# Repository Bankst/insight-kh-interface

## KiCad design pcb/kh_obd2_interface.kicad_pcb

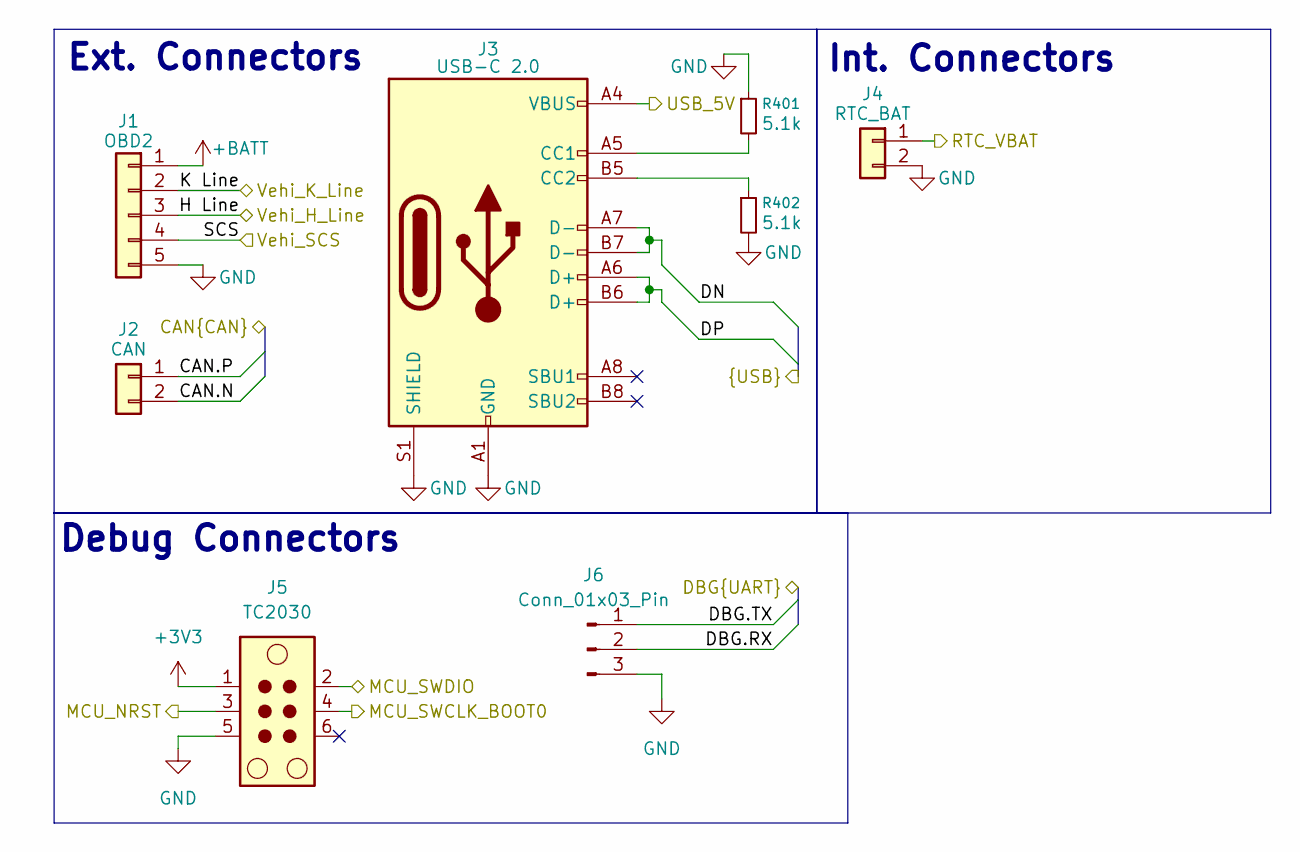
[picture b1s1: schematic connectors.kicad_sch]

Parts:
J1: OBD2; Molex_SL_171971-0005_1x05_P2.54mm_Vertical
J2: CAN; Molex_SL_171971-0002_1x02_P2.54mm_Vertical
J3: USB-C 2.0; USB_C_Receptacle_GCT_USB4105-xx-A_16P_TopMnt_Horizontal
J4: RTC_BAT; Molex_PicoBlade_53047-0210_1x02_P1.25mm_Vertical
J5: TC2030; Tag-Connect_TC2030-IDC-NL_2x03_P1.27mm_Vertical
J6: Conn_01x03_Pin; PinHeader_1x03_P2.54mm_Vertical_SMD_Pin1Left
R401, R402: 5.1k; R_0402_1005Metric

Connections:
+3V3: J5.1; also elsewhere on the board
+BATT: J1.1; also elsewhere on the board
/Communications/CAN.N: J2.2; also elsewhere on the board
/Communications/CAN.P: J2.1; also elsewhere on the board
/Connectors/DBG.RX: J6.2; also elsewhere on the board
/Connectors/DBG.TX: J6.1; also elsewhere on the board
/Connectors/DN: J3.A7 (D-), J3.B7 (D-); also elsewhere on the board
/Connectors/DP: J3.A6 (D+), J3.B6 (D+); also elsewhere on the board
/Connectors/H Line: J1.3; also elsewhere on the board
/Connectors/K Line: J1.2; also elsewhere on the board
/Connectors/MCU_NRST: J5.3; also elsewhere on the board
/Connectors/MCU_SWCLK_BOOT0: J5.4; also elsewhere on the board
/Connectors/MCU_SWDIO: J5.2; also elsewhere on the board
/Connectors/RTC_VBAT: J4.1; also elsewhere on the board
/Connectors/SCS: J1.4; also elsewhere on the board
/Connectors/USB_5V: J3.A4 (VBUS), J3.A9 (VBUS), J3.B4 (VBUS), J3.B9 (VBUS); also elsewhere on the board
GND: J1.5, J3.A1 (GND), J3.A12 (GND), J3.B1 (GND), J3.B12 (GND), J3.S1 (SHIELD), J4.2, J5.5, J6.3, R401.1, R402.2; also elsewhere on the board
unnamed: J3.A5 (CC1), R401.2
unnamed: J3.B5 (CC2), R402.1

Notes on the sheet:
Int. Connectors
Debug Connectors
Ext. Connectors

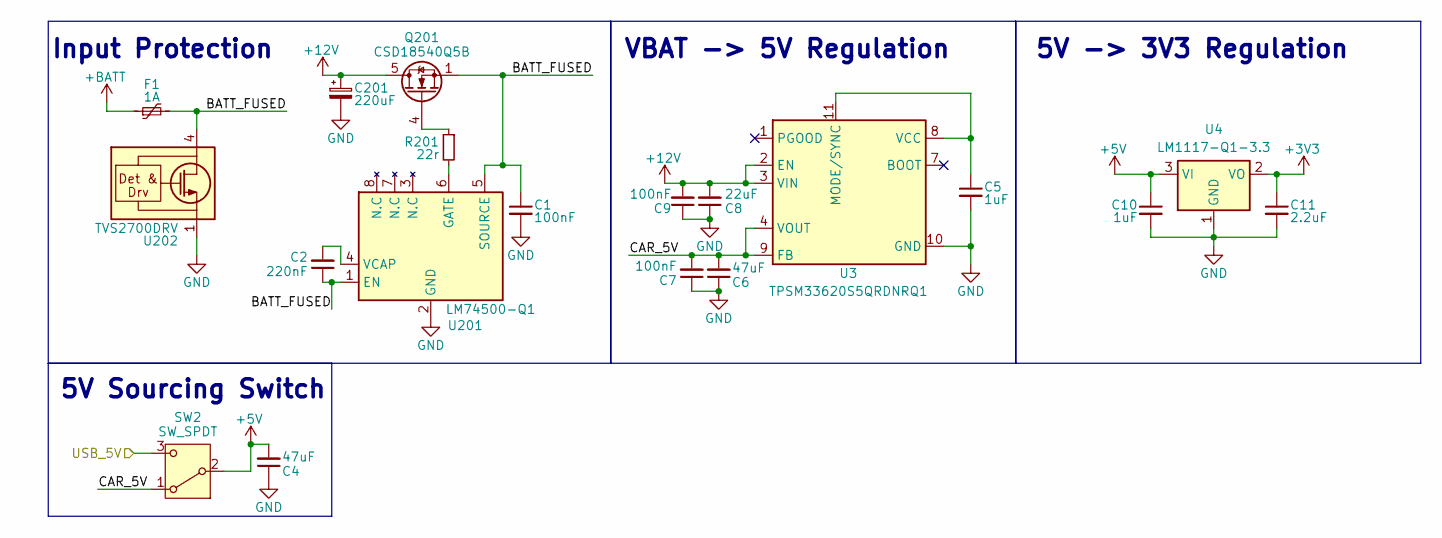
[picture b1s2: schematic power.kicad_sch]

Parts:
C1, C7, C9: 100nF; C_0402_1005Metric; Part C1005X5R1H104K050BB
C2: 220nF; C_0402_1005Metric
C4, C6: 47uF; C_1206_3216Metric; Part GRM31CR61A476KE15L
C5, C10: 1uF; C_0402_1005Metric; Part GRM155R71C104KA88D
C8: 22uF; C_1210_3225Metric; Part GRM32ER61E226KE15L
C11: 2.2uF; C_0402_1005Metric; Part GRM155R71C104KA88D
C201: 220uF; C_Elec_6.3x5.8; Part UWT1H221MNL1GS
F1: 1A; Fuse_1812_4532Metric; Part 1812L110/33MR
Q201: CSD18540Q5B; TDSON-8-1
R201: 22r; R_0402_1005Metric
SW2: SW_SPDT; PinHeader_1x03_P2.54mm_Vertical_SMD_Pin1Left
U3: TPSM33620S5QRDNRQ1; Texas_B3QFN-14-1EP_5x5.5mm_P0.65mm_ThermalVia
U4: LM1117-Q1-3.3; SOT-223-3_TabPin2; Part PLM111733QDCYRQ1
U201: LM74500-Q1; SOT-23-8
U202: TVS2700DRV; WSON-6-1EP_2x2mm_P0.65mm_EP1x1.6mm

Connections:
+3V3: C11.1, U4.2 (VO); also elsewhere on the board
+5V: C4.2, C10.1, SW2.2 (B), U4.3 (VI); also elsewhere on the board
+12V: C8.2, C9.2, C201.1, Q201.5 (D), U3.2 (EN), U3.3 (VIN); also elsewhere on the board
+BATT: F1.1; also elsewhere on the board
/Connectors/USB_5V: SW2.3 (C); also elsewhere on the board
/Power/BATT_FUSED: C1.1, C2.1, F1.2, Q201.1 (S), Q201.2 (S), Q201.3 (S), U201.1 (EN), U201.5 (SOURCE), U202.4 (IN), U202.5 (IN), U202.6 (IN)
/Power/CAR_5V: C6.2, C7.2, SW2.1 (A), U3.4 (VOUT), U3.9 (FB)
GND: C1.2, C4.1, C5.2, C6.1, C7.1, C8.1, C9.1, C10.2, C11.2, C201.2, U3.10 (GND), U4.1 (GND), U201.2 (GND), U202.1 (GND), U202.2 (GND), U202.3 (GND), U202.7 (GND); also elsewhere on the board
unnamed: Q201.4 (G), R201.1
unnamed: C5.1, U3.8 (VCC), U3.11 (MODE/SYNC)
unnamed: R201.2, U201.6 (GATE)
unnamed: C2.2, U201.4 (VCAP)

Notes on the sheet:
VBAT -> 5V Regulation
5V -> 3V3 Regulation
5V Sourcing Switch
Input Protection

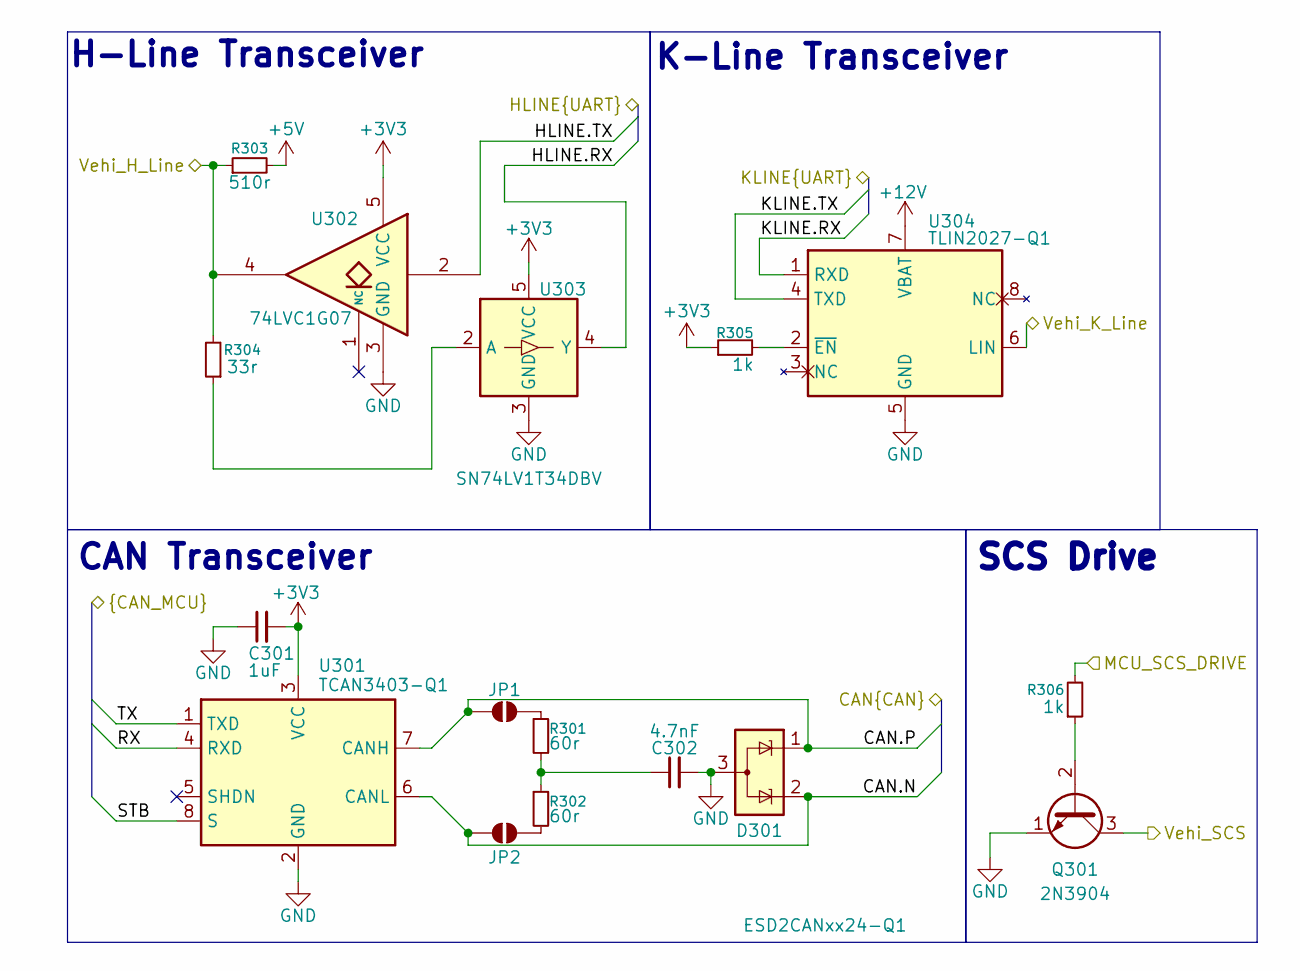
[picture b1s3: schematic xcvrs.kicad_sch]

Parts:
C301: 1uF; C_0402_1005Metric
C302: 4.7nF; C_0402_1005Metric
D301: ESD2CANxx24-Q1; SOT-23-3; Part ESD2CANFD24-Q1
JP1, JP2: SolderJumper_2_Open; SolderJumper-2_P1.3mm_Open_RoundedPad1.0x1.5mm
Q301: 2N3904; SOT-23
R301, R302: 60r; R_0402_1005Metric
R303: 510r; R_0402_1005Metric
R304: 33r; R_0402_1005Metric
R305, R306: 1k; R_0402_1005Metric
U301: TCAN3403-Q1; TSOT-23-8; Part TCAN3403DRQ1
U302: 74LVC1G07; Texas_R-PDSO-G5_DCK-5
U303: SN74LV1T34DBV; SOT-23-5
U304: TLIN2027-Q1; SOIC-8_3.9x4.9mm_P1.27mm

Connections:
+3V3: C301.2, R305.1, U301.3 (VCC), U302.5 (VCC), U303.5 (VCC); also elsewhere on the board
+5V: R303.2; also elsewhere on the board
+12V: U304.7 (VBAT); also elsewhere on the board
/Communications/CAN.N: D301.2 (K), JP2.2 (B), U301.6 (CANL); also elsewhere on the board
/Communications/CAN.P: D301.1 (K), JP1.1 (A), U301.7 (CANH); also elsewhere on the board
/Communications/HLINE.RX: U303.4 (Y); also elsewhere on the board
/Communications/HLINE.TX: U302.2; also elsewhere on the board
/Communications/KLINE.RX: U304.1 (RXD); also elsewhere on the board
/Communications/KLINE.TX: U304.4 (TXD); also elsewhere on the board
/Communications/MCU_SCS_DRIVE: R306.2; also elsewhere on the board
/Communications/RX: U301.4 (RXD); also elsewhere on the board
/Communications/STB: U301.8 (S); also elsewhere on the board
/Communications/TX: U301.1 (TXD); also elsewhere on the board
/Connectors/H Line: R303.1, R304.2, U302.4; also elsewhere on the board
/Connectors/K Line: U304.6 (LIN); also elsewhere on the board
/Connectors/SCS: Q301.3 (C); also elsewhere on the board
GND: C301.1, C302.2, D301.3 (A), Q301.1 (E), U301.2 (GND), U302.3 (GND), U303.3 (GND), U304.5 (GND); also elsewhere on the board
unnamed: C302.1, R301.2, R302.1
unnamed: JP1.2 (B), R301.1
unnamed: JP2.1 (A), R302.2
unnamed: Q301.2 (B), R306.1
unnamed: R304.1, U303.2 (A)
unnamed: R305.2, U304.2 (~EN)

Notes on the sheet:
CAN Transceiver
SCS Drive
K-Line Transceiver
H-Line Transceiver

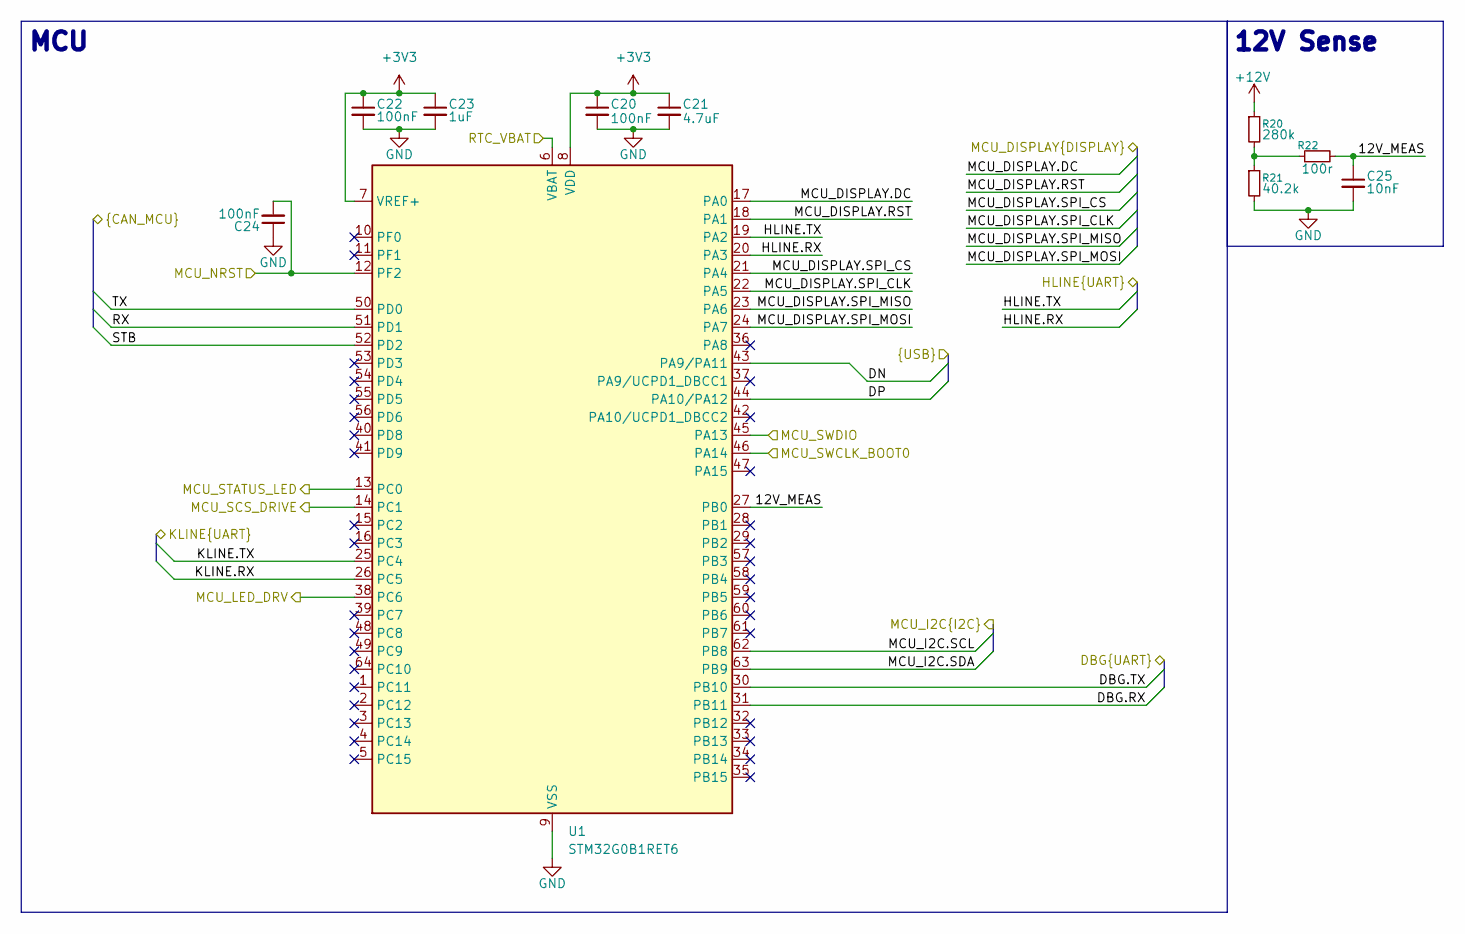
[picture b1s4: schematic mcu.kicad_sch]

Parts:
C20, C22, C24: 100nF; C_0402_1005Metric
C21: 4.7uF; C_0402_1005Metric
C23: 1uF; C_0402_1005Metric
C25: 10nF; C_0402_1005Metric
R20: 280k; R_0402_1005Metric
R21: 40.2k; R_0402_1005Metric
R22: 100r; R_0402_1005Metric
U1: STM32G0B1RET6; LQFP-64_10x10mm_P0.5mm

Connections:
+3V3: C20.1, C21.1, C22.1, C23.1, U1.7 (VREF+), U1.8 (VDD); also elsewhere on the board
+12V: R20.1; also elsewhere on the board
/Communications/HLINE.RX: U1.20 (PA3); also elsewhere on the board
/Communications/HLINE.TX: U1.19 (PA2); also elsewhere on the board
/Communications/KLINE.RX: U1.26 (PC5); also elsewhere on the board
/Communications/KLINE.TX: U1.25 (PC4); also elsewhere on the board
/Communications/MCU_SCS_DRIVE: U1.14 (PC1); also elsewhere on the board
/Communications/RX: U1.51 (PD1); also elsewhere on the board
/Communications/STB: U1.52 (PD2); also elsewhere on the board
/Communications/TX: U1.50 (PD0); also elsewhere on the board
/Connectors/DBG.RX: U1.31 (PB11); also elsewhere on the board
/Connectors/DBG.TX: U1.30 (PB10); also elsewhere on the board
/Connectors/DN: U1.43 (PA9/PA11); also elsewhere on the board
/Connectors/DP: U1.44 (PA10/PA12); also elsewhere on the board
/Connectors/MCU_NRST: C24.2, U1.12 (PF2); also elsewhere on the board
/Connectors/MCU_SWCLK_BOOT0: U1.46 (PA14); also elsewhere on the board
/Connectors/MCU_SWDIO: U1.45 (PA13); also elsewhere on the board
/Connectors/RTC_VBAT: U1.6 (VBAT); also elsewhere on the board
/HMI/MCU_LED_DRV: U1.38 (PC6); also elsewhere on the board
/HMI/MCU_STATUS_LED: U1.13 (PC0); also elsewhere on the board
/MCU/12V_MEAS: C25.1, R22.2, U1.27 (PB0)
/MCU/MCU_DISPLAY.DC: U1.17 (PA0)
/MCU/MCU_DISPLAY.RST: U1.18 (PA1)
/MCU/MCU_DISPLAY.SPI_CLK: U1.22 (PA5)
/MCU/MCU_DISPLAY.SPI_CS: U1.21 (PA4)
/MCU/MCU_DISPLAY.SPI_MISO: U1.23 (PA6)
/MCU/MCU_DISPLAY.SPI_MOSI: U1.24 (PA7)
/MCU/MCU_I2C.SCL: U1.62 (PB8)
/MCU/MCU_I2C.SDA: U1.63 (PB9)
GND: C20.2, C21.2, C22.2, C23.2, C24.1, C25.2, R21.2, U1.9 (VSS); also elsewhere on the board
unnamed: R20.2, R21.1, R22.1

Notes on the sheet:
12V Sense
MCU

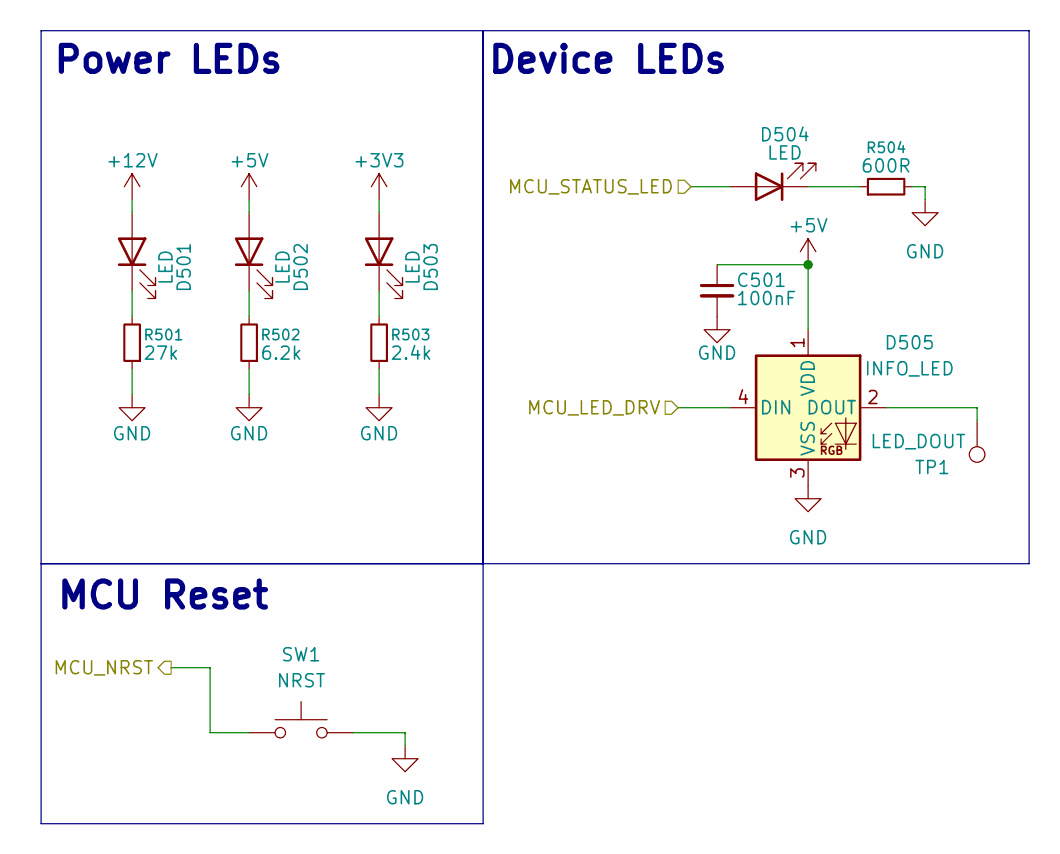
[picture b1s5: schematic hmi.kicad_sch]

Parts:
C501: 100nF; C_0402_1005Metric
D501, D502, D503, D504: LED; LED_0603_1608Metric
D505: INFO_LED; LED_WS2812B_PLCC4_5.0x5.0mm_P3.2mm
R501: 27k; R_0402_1005Metric
R502: 6.2k; R_0402_1005Metric
R503: 2.4k; R_0402_1005Metric
R504: 600R; R_0402_1005Metric
SW1: NRST; SW_Push_SPST_NO_Alps_SKRK
TP1: LED_DOUT; TestPoint_Pad_1.0x1.0mm

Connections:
+3V3: D503.2 (A); also elsewhere on the board
+5V: C501.1, D502.2 (A), D505.1 (VDD); also elsewhere on the board
+12V: D501.2 (A); also elsewhere on the board
/Connectors/MCU_NRST: SW1.1; also elsewhere on the board
/HMI/MCU_LED_DRV: D505.4 (DIN); also elsewhere on the board
/HMI/MCU_STATUS_LED: D504.2 (A); also elsewhere on the board
GND: C501.2, D505.3 (VSS), R501.1, R502.1, R503.1, R504.2, SW1.2; also elsewhere on the board
unnamed: D501.1 (K), R501.2
unnamed: D502.1 (K), R502.2
unnamed: D503.1 (K), R503.2
unnamed: D504.1 (K), R504.1
unnamed: D505.2 (DOUT), TP1.1

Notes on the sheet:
Power LEDs
Device LEDs
MCU Reset

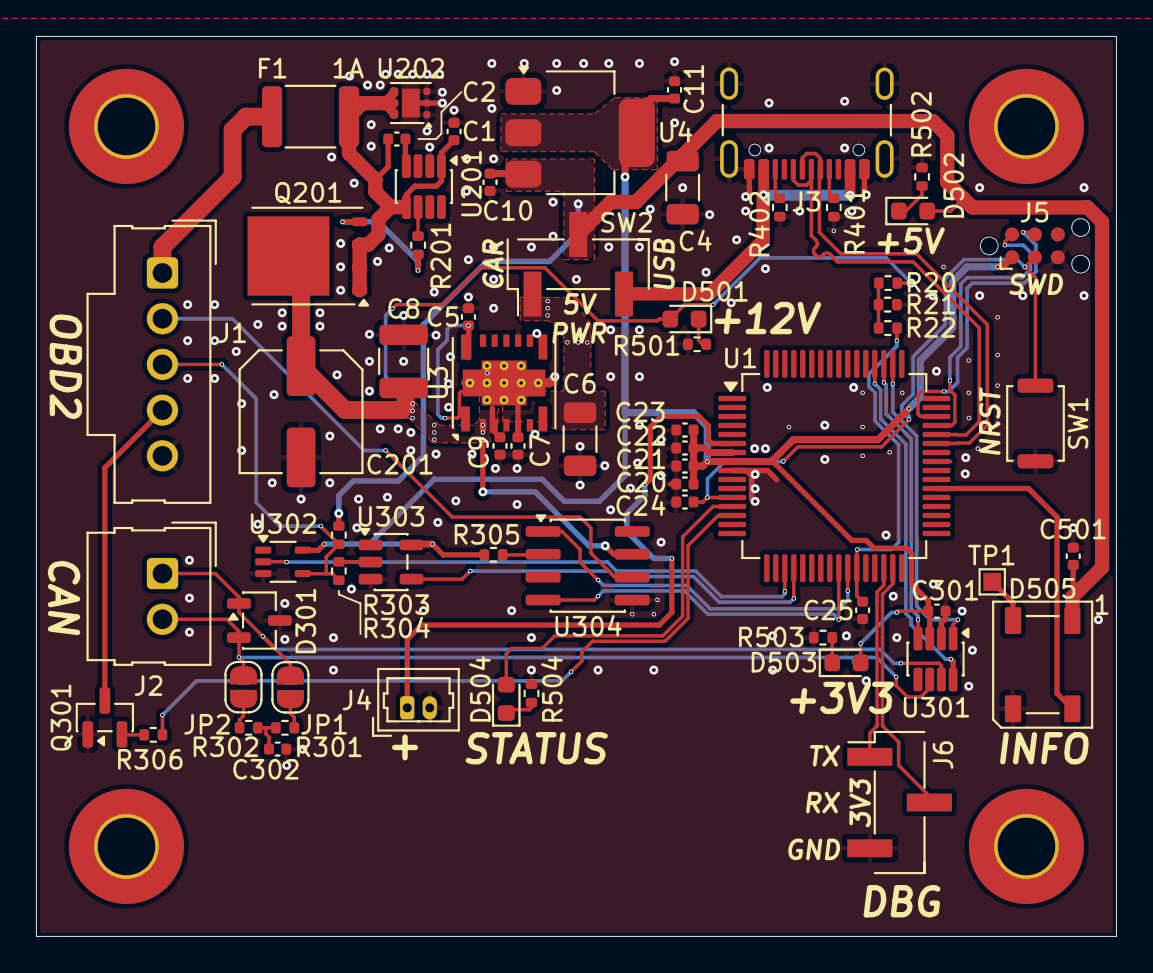
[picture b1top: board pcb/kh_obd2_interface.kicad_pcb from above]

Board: 2 copper layers, 60.0 x 50.0 mm, 69 parts (0 on the bottom side), 50 nets.

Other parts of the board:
M1, M1#2, M1#3, M1#4: MountingHole_3.2mm_M3_Pad_TopBottom

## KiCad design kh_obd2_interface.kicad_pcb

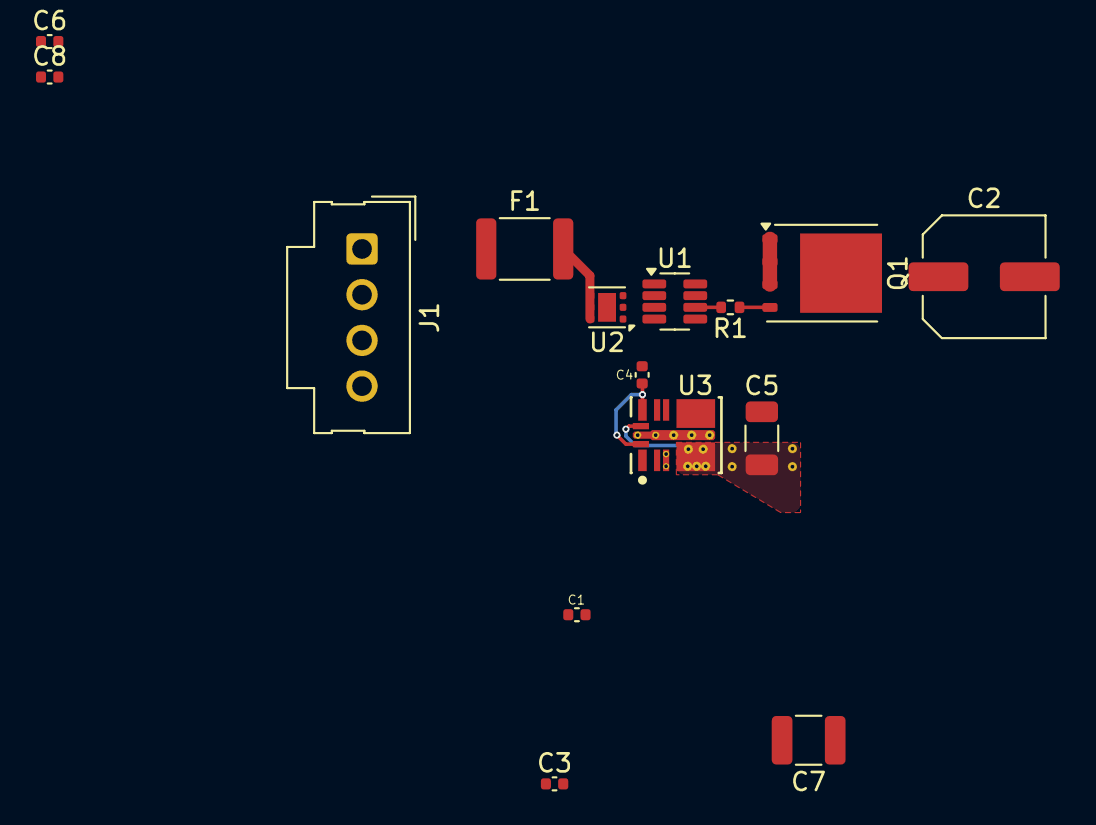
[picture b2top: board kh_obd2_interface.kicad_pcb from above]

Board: 2 copper layers, 15 parts (0 on the bottom side), 9 nets.

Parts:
C1, C6, C8: 100nF; C_0402_1005Metric
C2: 220uF; C_Elec_6.3x5.8
C3: 220nF; C_0402_1005Metric
C4: 1uF; C_0402_1005Metric
C5: 47uF; C_1206_3216Metric
C7: 22uF; C_1210_3225Metric
F1: 1A; Fuse_1812_4532Metric
J1: OBD2; Molex_SL_171971-0004_1x04_P2.54mm_Vertical
Q1: CSD18540Q5B; TDSON-8-1
R1: 22r; R_0402_1005Metric
U1: LM74500-Q1; SOT-23-8
U2: TVS2700DRV; WSON-6-1EP_2x2mm_P0.65mm_EP1x1.6mm
U3: TPSM33620S5QRDNRQ1; RDN0011A-MFG

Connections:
+5V: C5.2, C6.2, U3.4 (VOUT), U3.9 (FB)
+12V: C2.1, C7.2, C8.2, Q1.5 (D), U3.2 (EN), U3.3 (VIN)
+BATT: F1.1, J1.1
+BATT_FUSED: C1.1, C3.1, F1.2, Q1.1 (S), Q1.2 (S), Q1.3 (S), U1.1 (EN), U1.5 (SOURCE), U2.4 (IN), U2.5 (IN), U2.6 (IN)
GND: C1.2, C2.2, C4.2, C5.1, C6.1, C7.1, C8.1, U1.2 (GND), U2.1 (GND), U2.2 (GND), U2.3 (GND), U2.7 (GND), U3.10 (GND)
unnamed: Q1.4 (G), R1.1
unnamed: R1.2, U1.6 (GATE)
unnamed: C3.2, U1.4 (VCAP)
unnamed: C4.1, U3.8 (VCC), U3.11 (MODE/SYNC)

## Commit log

2025-09-26 Capacitor selections, reg schem done
2025-09-26 Some layout
2025-09-28 Move PCB to subfolder
2025-10-06 Heirarchal schematics, MCU, more layout
2025-10-07 pcb gitignore update, netting and mcu pinning
2025-10-07 add initial stm32 cmake project
2025-10-08 timer example compiles with make
2025-10-08 fucking finally
2025-10-14 add connectors schem
2025-10-14 add transceivers, routing, drc
2025-10-16 busses are hard
2025-10-16 Add TLIN2027, placement, DRC fixes, routing
2025-10-16 CAN/mcu placement/routing
2025-10-16 diff skew fixes, routing cleanups
2025-10-17 fix CAN tx/rx/stb, remove unused SWO
2025-10-17 moved EVERYTHING
2025-10-17 status/info leds, extra 5v cap
2025-10-28 dbg uart, nrst, SCS drive, etc
2025-10-29 connector prep
2025-10-30 USB reroute
2025-11-03 led dout testpoint
